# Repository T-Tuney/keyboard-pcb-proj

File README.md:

# keyboard-pcb-proj
im keyboard

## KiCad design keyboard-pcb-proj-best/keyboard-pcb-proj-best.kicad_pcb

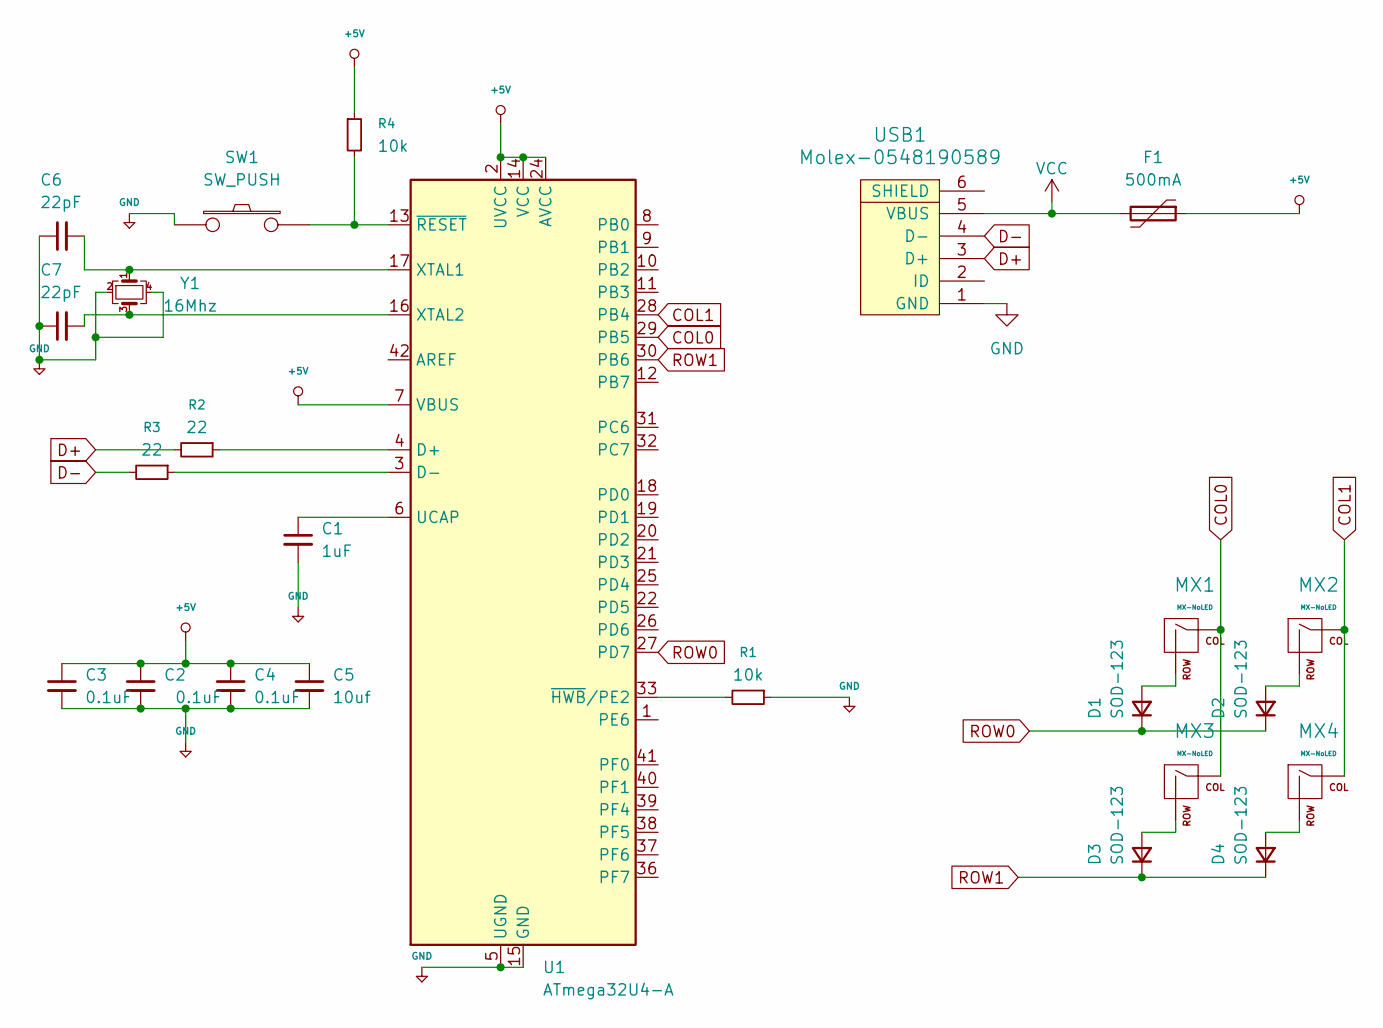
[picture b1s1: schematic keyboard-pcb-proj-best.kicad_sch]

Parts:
C1: 1uF; C_0805_2012Metric_Pad1.18x1.45mm_HandSolder
C2, C3, C4: 0.1uF; C_0805_2012Metric_Pad1.18x1.45mm_HandSolder
C5: 10uf; C_0805_2012Metric_Pad1.18x1.45mm_HandSolder
C6, C7: 22pF; C_0805_2012Metric_Pad1.18x1.45mm_HandSolder
D1, D2, D3, D4: SOD-123; D_SOD-123
F1: 500mA; Fuse_1206_3216Metric
MX1, MX2, MX3, MX4: MX-NoLED; MX-1U-NoLED
R1, R4: 10k; R_0805_2012Metric
R2, R3: 22; R_0805_2012Metric
SW1: SW_PUSH; SKQG-1155865
U1: ATmega32U4-A; TQFP-44_10x10mm_P0.8mm
USB1: Molex-0548190589
Y1: 16Mhz; Crystal_SMD_3225-4Pin_3.2x2.5mm

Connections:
+5V: C2.1, C3.1, C4.1, C5.1, F1.1, R4.1, U1.2 (UVCC), U1.7 (VBUS), U1.14 (VCC), U1.24 (AVCC), U1.34 (VCC), U1.44 (AVCC)
COL0: MX1.1 (COL), MX3.1 (COL), U1.29 (PB5)
COL1: MX2.1 (COL), MX4.1 (COL), U1.28 (PB4)
D+: R2.2, USB1.3 (D+)
D-: R3.2, USB1.4 (D-)
GND: C1.2, C2.2, C3.2, C4.2, C5.2, C6.1, C7.1, R1.1, SW1.1, U1.5 (UGND), U1.15 (GND), U1.23 (GND), U1.35 (GND), U1.43 (GND), USB1.1 (GND), Y1.2, Y1.4
unnamed: D1.2 (A), MX1.2 (ROW)
unnamed: D2.2 (A), MX2.2 (ROW)
unnamed: D3.2 (A), MX3.2 (ROW)
unnamed: D4.2 (A), MX4.2 (ROW)
unnamed: R2.1, U1.4 (D+)
unnamed: R3.1, U1.3 (D-)
unnamed: C1.1, U1.6 (UCAP)
unnamed: C6.2, U1.17 (XTAL1), Y1.1
unnamed: C7.2, U1.16 (XTAL2), Y1.3
unnamed: R1.2, U1.33 (~HWB/PE2)
unnamed: R4.2, SW1.2, U1.13 (~RESET)
ROW0: D1.1 (K), D2.1 (K), U1.27 (PD7)
ROW1: D3.1 (K), D4.1 (K), U1.30 (PB6)
VCC: F1.2, USB1.5 (VBUS)

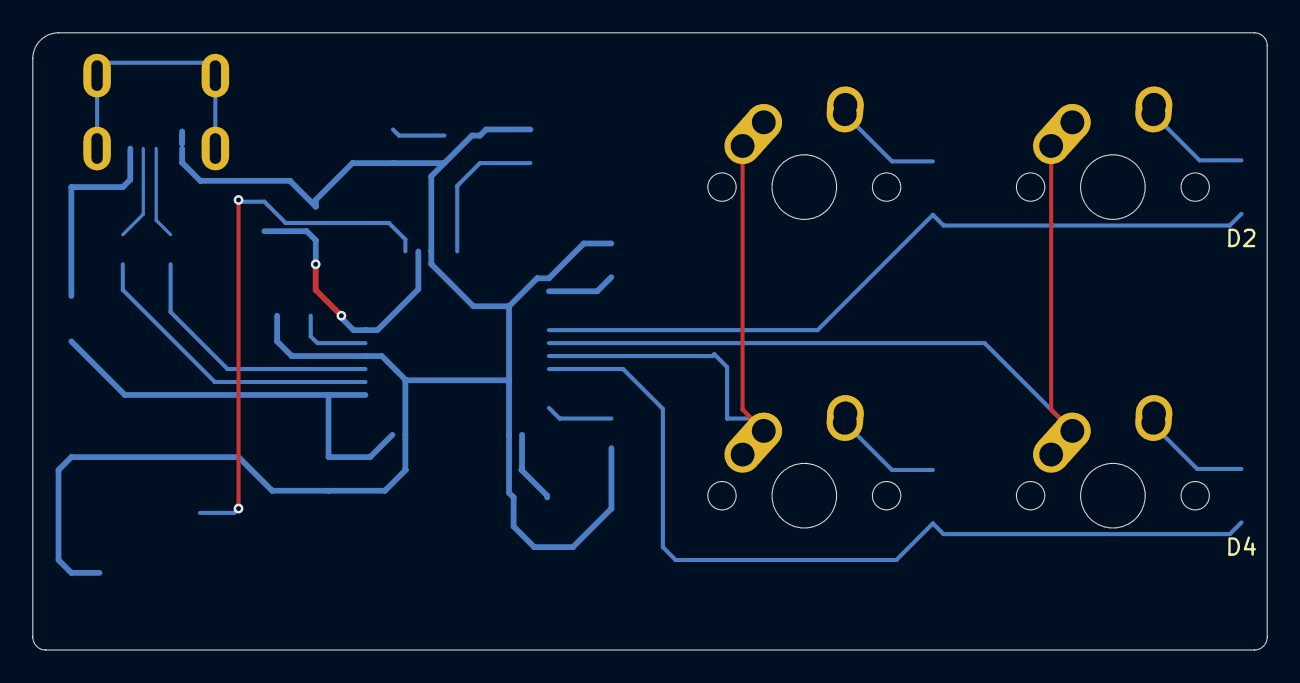
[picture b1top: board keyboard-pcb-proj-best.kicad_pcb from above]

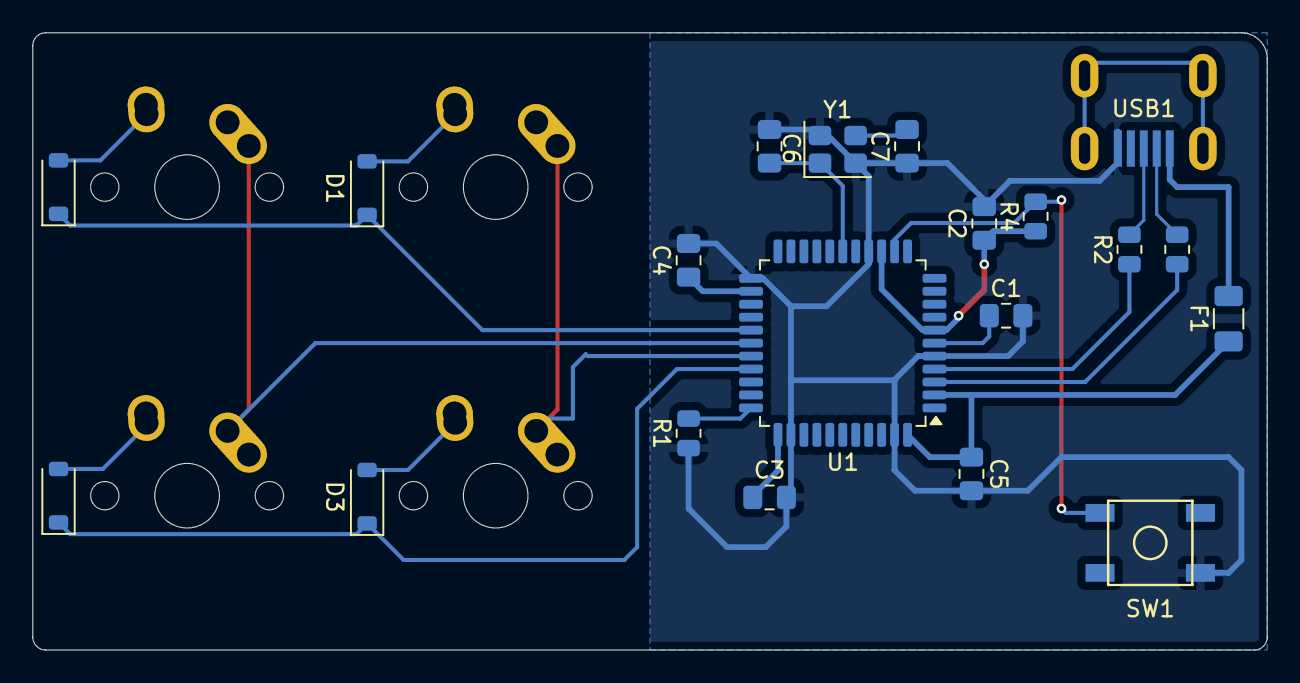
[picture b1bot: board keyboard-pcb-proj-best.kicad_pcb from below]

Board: 2 copper layers, 76.2 x 38.1 mm, 24 parts (20 on the bottom side), 20 nets.

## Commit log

2026-03-04 KiCad Project Intilization
2026-03-04 Added submodules
2026-03-04 Added Footprint libraries
2026-03-04 Built Schematic
2026-03-04 Created PCB
    Still need to finish routing
2026-03-04 pcb routing
2026-03-04 Finished Routing
2026-03-04 Minor Routing Changes
2026-03-05 Finalized Routing and Matrix Pin Out
2026-03-05 Completed Board Design
2026-03-06 PCB design rework started
2026-03-10 Finished rerouting
2026-03-10 Finalized Rerouting
2026-03-11 fixing errors
2026-03-11 Fixed Most Errors
2026-03-16 error corrections
